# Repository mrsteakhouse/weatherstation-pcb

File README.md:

# Weather station PCB Schematics 

These are the PCB schematics for the weatherstation project.
It is designed to work with an ESP-01 tuned for deep sleep.
The circuit is powered by any 9V power source (6xAA works best).
A linear voltage regulator ([MCP1755S](http://ww1.microchip.com/downloads/en/devicedoc/25160a.pdf)) breaks that 9V down to 3.3V.
The MCU communicates through I2C with the on board voltage sensor ([MCP3421](https://www.microchip.com/wwwproducts/en/en520011)) and an air quality sensor like the [BME-280](https://www.bosch-sensortec.com/products/environmental-sensors/humidity-sensors-bme280/).
Additionaly any other I2C device that runs on 3.3V may be connected through an extra pair of VCC, GND, SCL and SDA.

The implementation can be found [here](https://github.com/mrsteakhouse/weatherstation/tree/main).

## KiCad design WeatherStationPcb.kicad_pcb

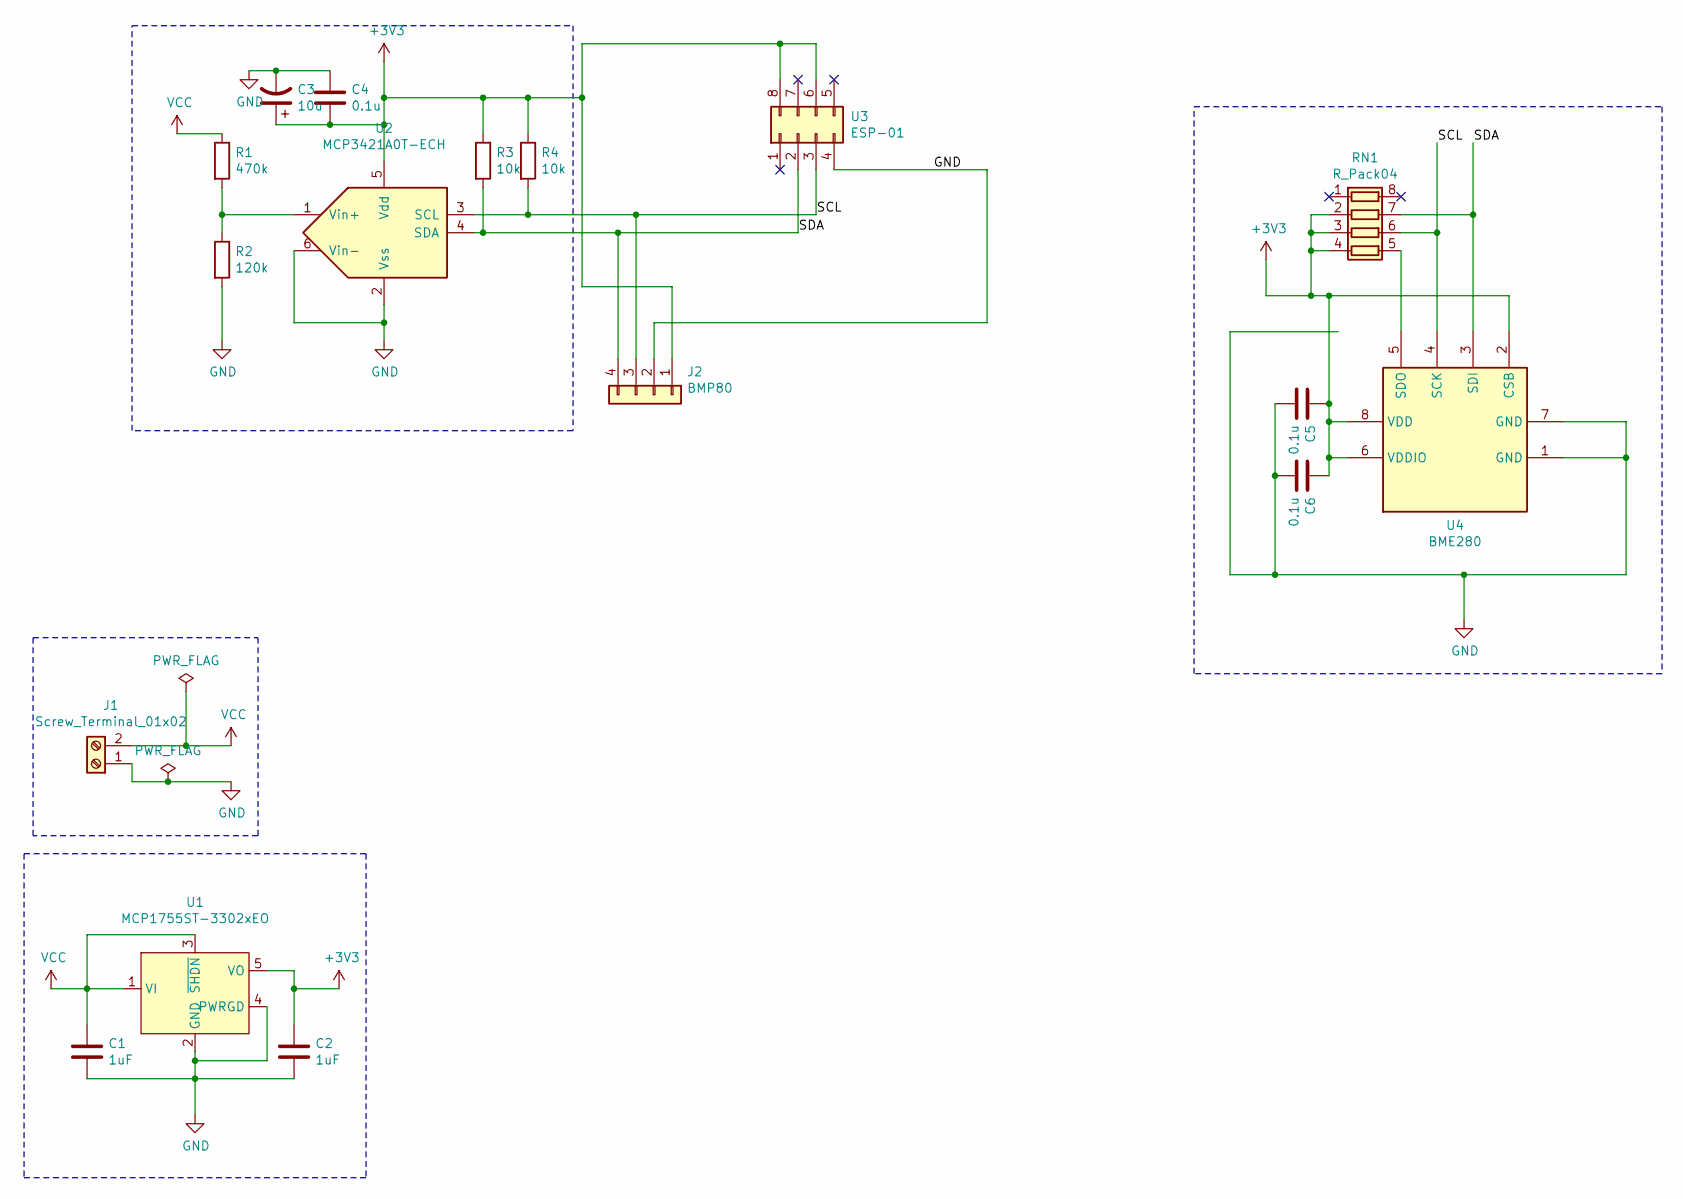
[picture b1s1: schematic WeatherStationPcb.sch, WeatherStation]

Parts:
C1, C2: 1uF; C_0805_2012Metric
C3: 10u; CP_EIA-6032-28_Kemet-C
C4, C5, C6: 0.1u; C_0805_2012Metric
J1: Screw_Terminal_01x02; TerminalBlock_bornier-2_P5.08mm
J2: BMP80; PinSocket_1x04_P2.54mm_Vertical
R1: 470k; R_0805_2012Metric
R2: 120k; R_0805_2012Metric
R3, R4: 10k; R_0805_2012Metric
RN1: R_Pack04; R_Array_Convex_4x0603
U1: MCP1755ST-3302xEO; SOT-23-5
U2: MCP3421A0T-ECH; SOT-23-6
U3: ESP-01
U4: BME280; Bosch_LGA-8_2.5x2.5mm_P0.65mm_ClockwisePinNumbering

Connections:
+3V3: C2.1, C3.1, C4.1, C5.2, C6.2, J2.1, R3.1, R4.1, RN1.2 (R2.1), RN1.3 (R3.1), RN1.4 (R4.1), U1.5 (VO), U2.5 (Vdd), U3.6 (CH_PD), U3.8 (VCC), U4.2 (CSB), U4.6 (VDDIO), U4.8 (VDD)
/SCL: J2.3, R4.2, RN1.6 (R3.2), U2.3 (SCL), U3.3 (GPIO2), U4.4 (SCK)
/SDA: J2.4, R3.2, RN1.7 (R2.2), U2.4 (SDA), U3.2 (GPIO0), U4.3 (SDI)
GND: C1.2, C2.2, C3.2, C4.2, C5.1, C6.1, J1.1, J2.2, R2.2, U1.2 (GND), U1.4 (PWRGD), U2.2 (Vss), U2.6 (Vin-), U3.4 (GND), U4.1 (GND), U4.7 (GND)
unnamed: R1.2, R2.1, U2.1 (Vin+)
unnamed: RN1.5 (R4.2), U4.5 (SDO)
VCC: C1.1, J1.2, R1.1, U1.1 (VI), U1.3 (~SHDN)

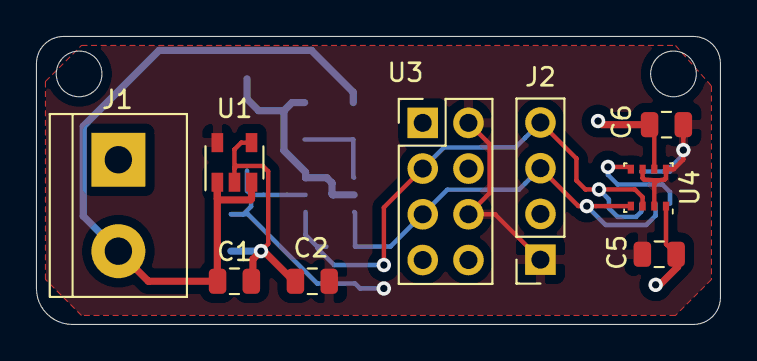
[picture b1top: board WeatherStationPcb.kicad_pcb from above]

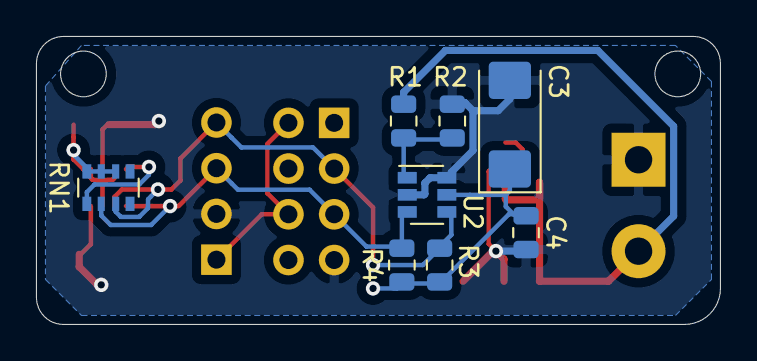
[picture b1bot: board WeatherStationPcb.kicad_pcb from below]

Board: 2 copper layers, 38.0 x 16.0 mm, 17 parts (8 on the bottom side), 7 nets.

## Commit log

2020-12-23 make its own repository for pcb files
